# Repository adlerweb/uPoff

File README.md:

# µPoff - External deep sleep circuit
*µPoff* is a circuit placed high-side between your power source and your microcontroller. It is designed to cut power to the µC until a external sensor activates it. Additionally a onboard RTC can wake the µC in programmed intervals.

It is mainly aimed at battery powered sensor applications like door sensors, which also should report their battery level and presence regularly.

## Pinout

## PCB
### 0402 Component Package 

### 0603 Component Package 

## Connecting your µC

Remove the positive connection between your power source and µC. Connect the battery to **VCC** and your µC to **OUT**. Additionally connect **GND** to your existing ground. The external sensor should pull **^SW** low to activate the circuit. Lastly run a wire between one of your GPIO-Pins and **ON**. If you want to use the included RTC you'll also need to connect the I²C-Lines **SDA** and **SCL**. On AVR and STM32 based microcontrollers you'll have to use the predefined I²C pins, on ESP8266, ESP32 you can use any free GPIO.

## Software control

Usually power only stays on as long as **^ON** is low, however most tasks take longer to complete. To keep power on it is crucial to drive **ON** high as soon as your µC is started. When finished you can turn off power by driving **ON** LOW.

### Dependencies

 * Wire.h (usually included)
 * elpaso Rtc_Pcf8563 (https://github.com/elpaso/Rtc_Pcf8563)

### Manual wake only
```
#include "upoff.h"
UPOFF upoff;

void setup() {
  upoff.on(D1); //ON connected to D1
}

void loop() {
  //do something
  upoff.off();
}
```

### Manual and timed wake

```
#include "upoff.h"
UPOFF upoff;

bool reason;

void setup() {
  reason = upoff.on(D1, D2, D3); //D1 = ON; D2 = SDA; D3 = SCL
  //reason = upoff.on(D1, true); //Use predefined I²C-Pins

  /* Set clock */
  while(!upoff.isValid(false)) {
    upoff.setTime(20, 02, 02, 02, 02, 02); //2020-02-02 02:02:02
    yield();
  }
}

void loop() {
  pinMode(LED_BUILTIN, OUTPUT);
  if(reason) {
    /* either first boot or caused by RTC */
    byte loops=5;
    while(loops > 0) {
      digitalWrite(LED_BUILTIN, LOW);
      delay(100);
      digitalWrite(LED_BUILTIN, HIGH);
      delay(100);
      loops--;
    }
  }else{
    /* manual trigger */
    digitalWrite(LED_BUILTIN, LOW);
    delay(1000);
    digitalWrite(LED_BUILTIN, HIGH);
    delay(1000);
  }

  /* Sleep for 15 seconds */
  upoff.off(15);
}
```

## Power
While sleeping current draw for *µPoff* is ~10µA. Output should be fine for up to 1A.

## Common problems

### Boot-time vs. signal time
The external sensor has to keep **^ON** low until the µC is running and driving **ON**. Some µCs take several hundreds of milliseconds to boot. If your sensors pulse is too short you might be able to stretch it using some R+C magic.

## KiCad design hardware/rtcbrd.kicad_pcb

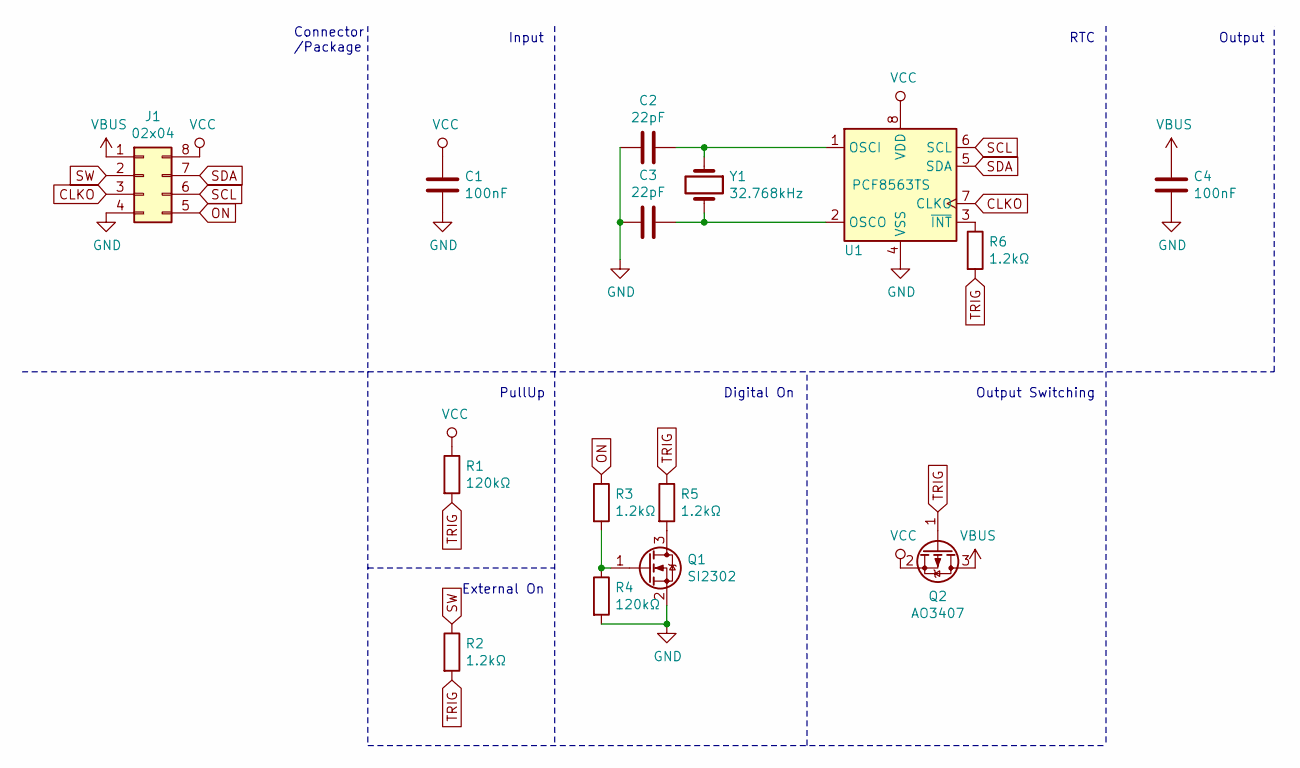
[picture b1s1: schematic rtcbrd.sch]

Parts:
C1, C4: 100nF; C_0402
C2, C3: 22pF; C_0402
J1: 02x04; DIP-8_W7.62mm
Q1: SI2302; SOT-23
Q2: AO3407; SOT-23
R1, R4: 120kΩ; R_0402
R2, R3, R5, R6: 1.2kΩ; R_0402
U1: PCF8563TS; HTSOP-8-1EP_3.9x4.9mm_Pitch1.27mm
Y1: 32.768kHz; Crystal_C38-LF_d3.0mm_l8.0mm_Horizontal

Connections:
CLKO: J1.3, U1.7 (CLKO)
GND: C1.1, C2.2, C3.2, C4.1, J1.4, Q1.2 (S), R4.2, U1.4 (VSS)
unnamed: C2.1, U1.1 (OSCI), Y1.1
unnamed: C3.1, U1.2 (OSCO), Y1.2
unnamed: Q1.1 (G), R3.2, R4.1
unnamed: Q1.3 (D), R5.2
unnamed: R6.1, U1.3 (~INT~)
ON: J1.5, R3.1
SCL: J1.6, U1.6 (SCL); also elsewhere on the board
SDA: J1.7, U1.5 (SDA); also elsewhere on the board
SW: J1.2, R2.1
TRIG: Q2.1 (G), R1.2, R2.2, R5.1, R6.2
VBUS: C4.2, J1.1, Q2.3 (D)
VCC: C1.2, J1.8, Q2.2 (S), R1.1, U1.8 (VDD); also elsewhere on the board

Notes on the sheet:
Connector /Package
Input
RTC
Output
Output Switching
Digital On
PullUp
External On

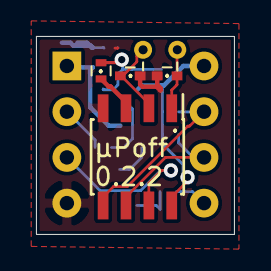
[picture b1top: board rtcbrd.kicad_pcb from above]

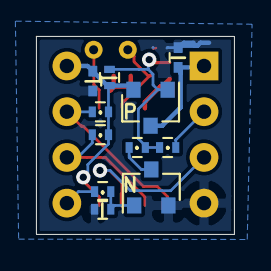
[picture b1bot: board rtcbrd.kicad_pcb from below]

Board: 2 copper layers, 11.0 x 11.0 mm, 17 parts (11 on the bottom side), 14 nets.

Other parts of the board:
R7, R8: 1.2kΩ; R_0402

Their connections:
SCL: R8.2; also elsewhere on the board
SDA: R7.2; also elsewhere on the board
VCC: R7.1, R8.1; also elsewhere on the board

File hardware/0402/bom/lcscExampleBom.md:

Reference | Quantity | Footprint | Value | LCSC #
-- | -- | -- | -- | --
C1,C4 | 2 | 0402 | 100nF | C1525
C2,C3 | 2 | 0402 | 22pF | C115618
R2,R3,R5,R6 | 4 | 0402 | 1.2kΩ | C100581
R1,R4 | 2 | 0402 | 120kΩ | C384380
U1 | 1 | HTSOP8 | PCF8563TS | C269877
Y1 | 1 | C38 | 32.768kHz | C52082
Q1 | 1 | SOT-23 | SI2302 | C351399
Q2 | 1 | SOT-23 | AO3407 | C351408

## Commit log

2020-02-09 Update Copyright
2020-02-09 Add Readme
2020-02-09 Add Library description
2020-02-09 Add I²C-Info for AVR/STM32 vs ESP*
2020-02-09 Dependencies
2020-02-19 IMPORT
2020-02-23 Do not ignore BOM
2020-02-25 Add I²C Pull-Up; Move value markings
2020-04-16 new Folder for original 0403
2020-04-17 new Folder for original 0402
2020-04-18 PCB 0402 top picture
2020-04-18 Add PCB Files from EasyEDA
    not tested in hardware jet
2020-07-28 Fix incorrect validity check
    Rumors say midnight is in fact a valid time. Too much copy&paste. Fixes #6.
2023-06-01 Improved comments
